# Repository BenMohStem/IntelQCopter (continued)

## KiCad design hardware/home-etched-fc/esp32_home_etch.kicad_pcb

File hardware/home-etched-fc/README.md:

# ESP32-S3 single-sided flight-controller carrier

## Current edition: photographed sensor headers, 23 October 2026

This replaces the earlier four-wire sensor ports. The old PCB, mask and README are preserved in `../../archive/hardware/2026-10-23-before-photo-headers/previous-carrier.zip`. Old extracted ZIP folders are **not** current fabrication files.

- [Open native KiCad PCB](esp32_home_etch.kicad_pcb) and [schematic](esp32_home_etch.kicad_sch).
- [Current complete KiCad ZIP](output/IntelQCopter-ESP32-home-etch-KiCad.zip).
- [Three identical text-free A4 masks, 1:1](output/pdf/etch-mask-3-copies-A4-1to1.pdf).
- [Assembly view](assembly-preview.png), [pin map](connector-map.md), [jumper list](wire-links.csv), [drill coordinates](drill-table.csv).
- [Current original audit results](../../artifacts/hardware/photo-headers-20261023/README.md).

**PCB: 100 x 100 mm; route and etch B.Cu only.** KiCad stores a two-copper-layer board because its file format uses paired copper layers; there are no front-copper routes, vias or plated-layer connections required. All crossings use insulated top wires. Ground is a large solid B.Cu fill, with solid pad joins and circular drill openings, no thermal crosses. Copper under the DevKit antenna region is removed.

## Headers and the photographs

Component-side view. Pin1 of each sensor row is its leftmost pad at x=8 mm; pin numbers increase to the right. These are **2.54 mm solder/header landings** in the photographed signal order, not verified body/mounting-hole models. Mount the sensor boards separately and solder wires signal-to-signal. Do not flip a module onto the carrier just because its pin count matches: the photo may show its opposite face, and its body may overlap neighbouring parts.

| Carrier | Module | Pins1 through last, left to right |
|---|---|---|
| J4, y=45 mm | GY-521 MPU6050, 8 pins | VCC=3.3V; GND; SCL=GPIO8; SDA=GPIO9; XDA unused; XCL unused; AD0=GND; INT unused |
| J5, y=55 mm | GY-BM280, 6 pins | VCC=3.3V; GND; SCL=GPIO8; SDA=GPIO9; CSB=3.3V **through W24**; SDO=GND |
| J6, y=75 mm | GY-271/HW-246, 5 pins | VCC=3.3V; GND; SCL=GPIO8; SDA=GPIO9; DRDY unused |

The MPU screenshot reads INT,AD0,XCL,XDA,SDA,SCL,GND,VCC from its shown left to right. Start wiring from the printed **VCC** end; do not count from the photograph's left edge. The barometer photo reads VCC,GND,SCL,SDA,CSB,SDO from top to bottom. The magnetometer in the hand photo reads VCC,GND,SCL,SDA,DRDY top to bottom. Unused pins get isolated solder pads; they are not joined to the ground plane.

BMP280 CSB must be high for I2C; W24 provides that connection. SDO low selects0x76. MPU AD0 low selects0x68. The GY-271 label does not establish which magnetometer silicon a seller fitted; confirm HMC5883L versus QMC5883L by chip ID/address before selecting its driver. No firmware driver completion is claimed here.

### LiDAR J13: four large wire-solder holes

The official TOFSense F2 Mini uses four wires. This carrier keeps generous5.08mm spacing,3.2mm round pads and1.2mm drills, so no tiny GH connector is needed on the PCB.

| J13 pin | Carrier signal | Connect LiDAR wire labelled |
|---|---|---|
| 1 | Common GND | GND |
| 2 | Regulated5V via W23 | VCC |
| 3 | FC RX / GPIO6 | LiDAR TX |
| 4 | FC TX / GPIO7 | LiDAR RX |

This is a wire landing order, **not** the pin order of the tiny LiDAR plug. Follow the signal labels and official plug diagram. The real F2 Mini reference is four pins; a different five-wire device needs its model/label checked before its fifth wire is assigned. Do not guess a fifth power or mode signal.

## ESP32-S3 assignments

The carrier fits the genuine/reference **Espressif ESP32-S3-DevKitC-1, 2x22 pins**,22.86mm row spacing,2.54mm pitch. A different ESP32-S3 clone is not guaranteed to fit. The chip datasheet specifies GPIO functions; the **DevKit** documentation determines header positions. All four published DevKit GND header pins connect directly to the common copper.

| Function | GPIO | Notes |
|---|---|---|
| Shared I2C SDA / SCL | 9 / 8 | 3.3V pull-ups only |
| ESC FL / FR / RR / RL signal | 12 / 1 / 2 / 14 | Through220ohm; ESC grounds common, no ESC power carried |
| Companion UART TX / RX | 17 / 18 | J12 pins1/2; companion RX/TX respectively; pin3GND |
| LiDAR UART RX / TX | 6 / 7 | J13 pins3/4; UART levels3.3V |
| Battery voltage ADC / current ADC | 4 / 5 | Low-current measurement only |

Assignments keep the existing project firmware GPIO mapping; **no firmware changes are included in this PCB revision**. Avoid using a raw ESP32 chip pin number as a DevKit header number. Boot straps, USB and flash/PSRAM pins are not used for these signals. The current project LiDAR/magnetometer hardware interfaces remain unvalidated. Motor arming remains disabled.

## Supply and assembly

1. Fit **all14 insulated wire links** exactly as `wire-links.csv`, including W24 for BMP280 CSB. A colour line in the assembly image is a real insulated wire, never a copper track on the component side.
2. J3 accepts an **external regulated5V** source. Never connect a3S pack directly there. Motor/ESC current goes through the separate rated PDB. This carrier is not a high-current battery switch or BMS.
3. W21 connects external5V to the DevKit5V input. **Remove W21 before powering the DevKit by USB**. W23 supplies LiDAR5V from the external regulator, not from the3.3V sensor rail.
4. Sensor VCC and I2C logic are3.3V. Check voltage at each actual module's chip supply after its onboard regulator; unknown breakout LDOs may drop too much voltage from3.3V input. No5V I2C pull-up is acceptable at ESP32 GPIOs. Check combined parallel module pull-ups; remove redundant ones if the measured equivalent resistance exceeds the bus sink-current capability. At3.3V,1kohm draws about2.9mA at a0.4V low level.
5. J7 is pack-voltage **sense only**.47kohm/10kohm gives approximately2.21V at12.6V pack voltage, followed by1kohm/100nF filtering. Disconnect sense when the MCU is unpowered; no powered-off clamp isolation is provided. J14 expects a conditioned0-2.5V current signal; its external transducer has not been selected.
6. Use the fit/drill sheet and actual parts before etching.2.54mm rows require smaller1.94mm pads/1.1mm holes to preserve0.60mm copper gaps. Other wire pads are3.2mm/1.2mm. Tracks are at least0.8mm; signal tracks normally1mm. Hand drilling still needs centring.

## Print and etch

Print the **current** PDF with **Actual size /100%**, no fit-to-page. It contains3 copies, no text. Black is retained copper, white is removed copper, and drill centres stay white. The artwork is component-view orientation; pressing the toner side face-down onto bottom copper supplies the required reversal. Do not apply a second mirror. Measure22.86mm between the two DevKit header rows, or the separate20mm calibration ruler before transfer; there is no board-edge line in the text-free mask. Digital1:1 scale is checked; your printer's physical output is not measured here.

Refresh the native B.Cu zone in KiCad with `B` after editing. For a native plot use B.Cu only, black positive, board scale1.0, disable footprint values/references and plot drill marks. The delivered PDF is generated directly from filled native copper and subtracts complete white drill circles; it does not include silkscreen or thermal relief crosses.

## Evidence and remaining limits

Native KiCad DRC/ERC, schematic/netlist comparison and rendered-mask checks report actual results in the dated evidence directory. They check the digital board and explicit wire links. They do not validate unknown module internals, physical fit, regulator performance, a manufactured board, RF behaviour or flight safety. No flight/hardware test was performed for this PCB correction.

References: [Espressif DevKit header map](https://docs.espressif.com/projects/esp-dev-kits/en/latest/esp32s3/esp32-s3-devkitc-1/user_guide_v1.0.html), [ESP32-S3 datasheet](https://www.espressif.com/sites/default/files/documentation/esp32-s3_datasheet_en.pdf), [Bosch BMP280 I2C circuit](https://www.bosch-sensortec.com/media/boschsensortec/downloads/datasheets/bst-bmp280-ds001.pdf), [Nooploop wire sequence](https://support.nooploop.com/tofsense/hardware/). Sensor breakout signal order additionally follows the user photos; personal screenshots are not published.

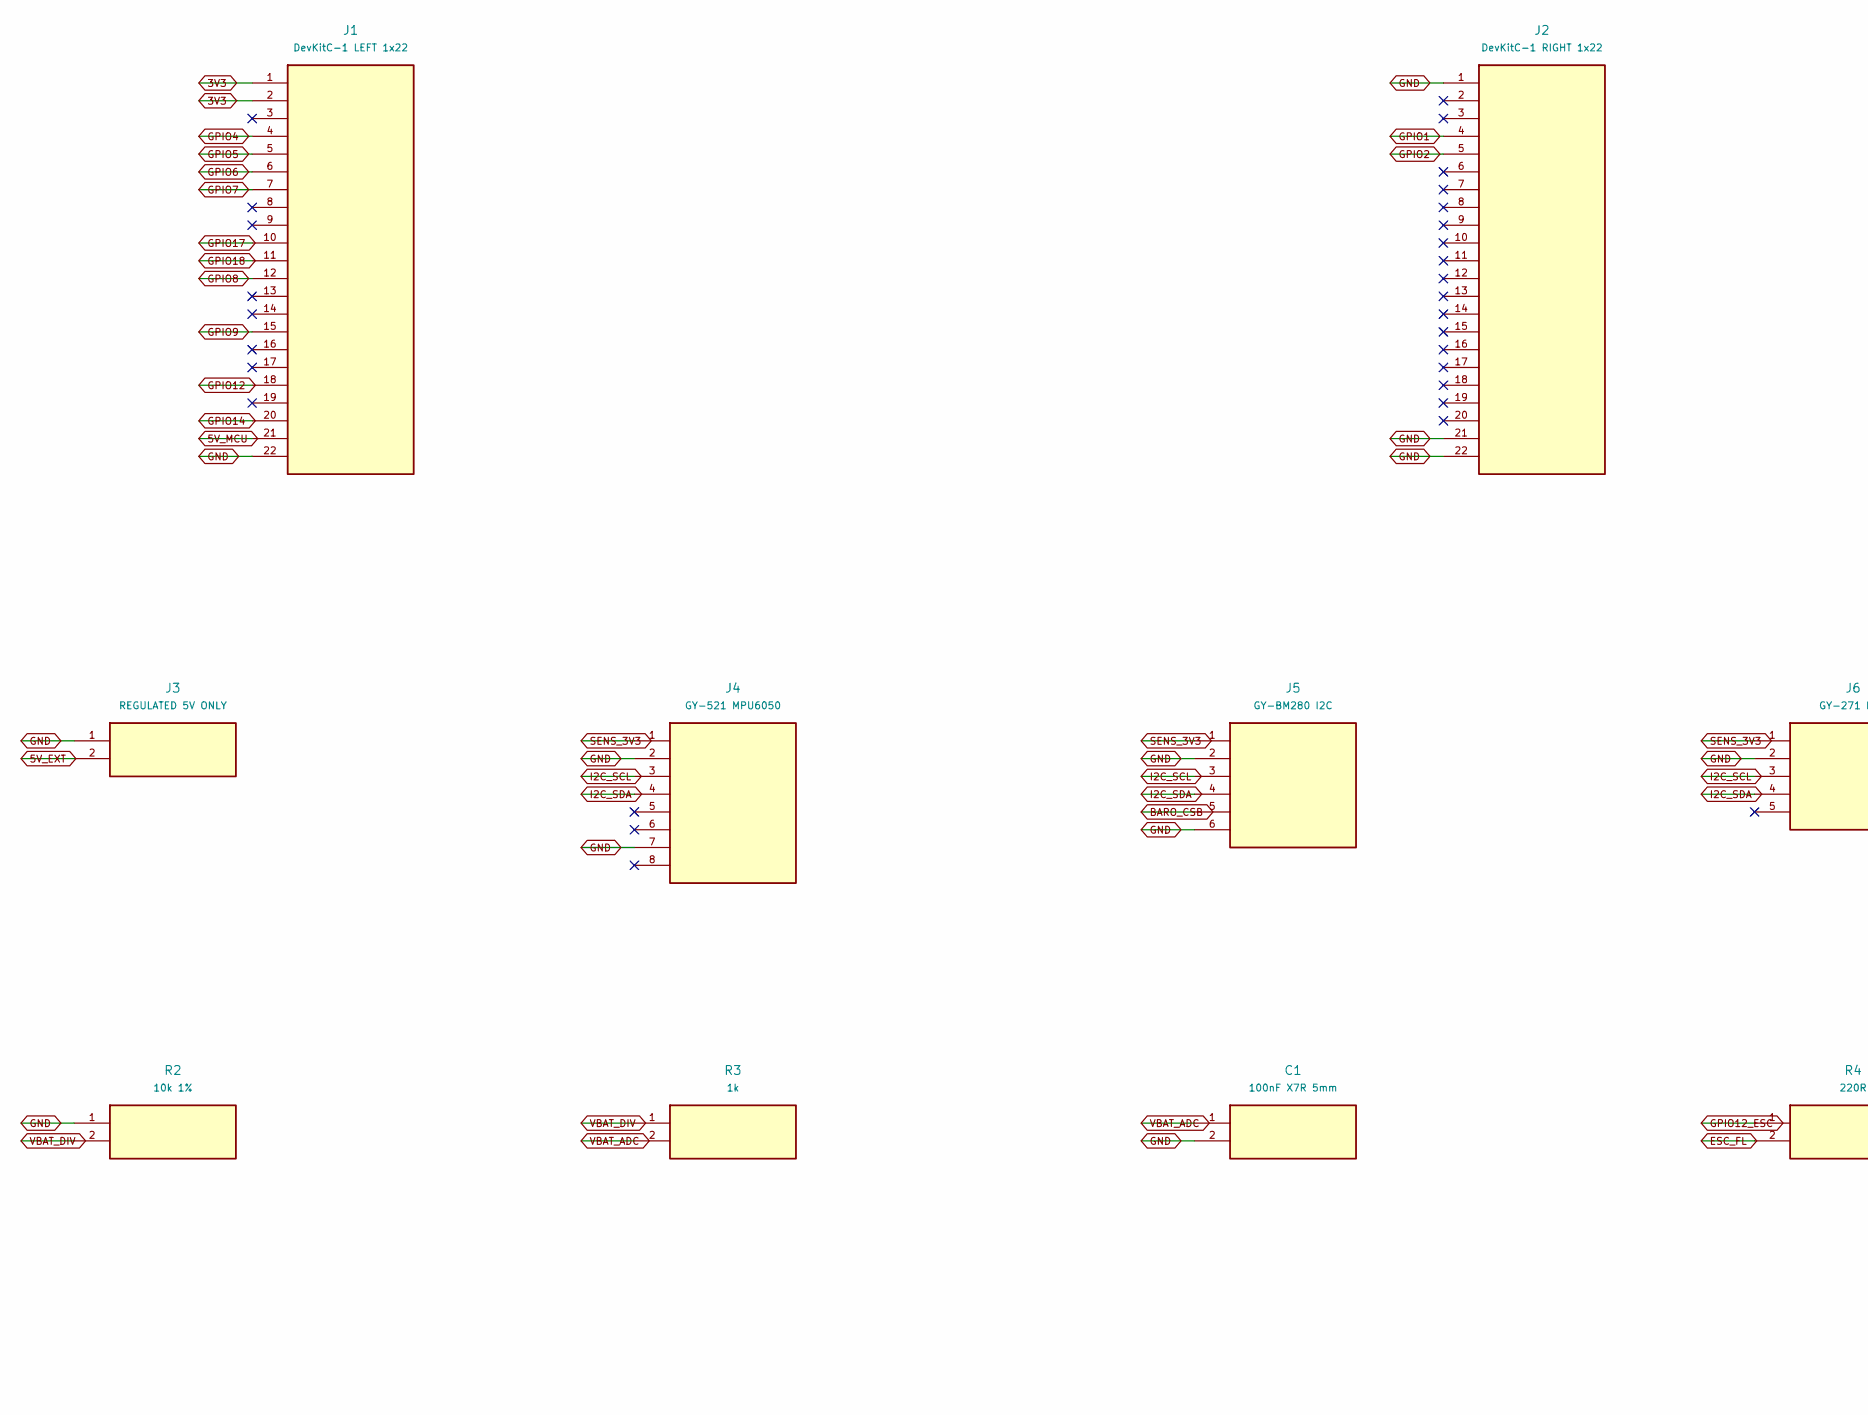
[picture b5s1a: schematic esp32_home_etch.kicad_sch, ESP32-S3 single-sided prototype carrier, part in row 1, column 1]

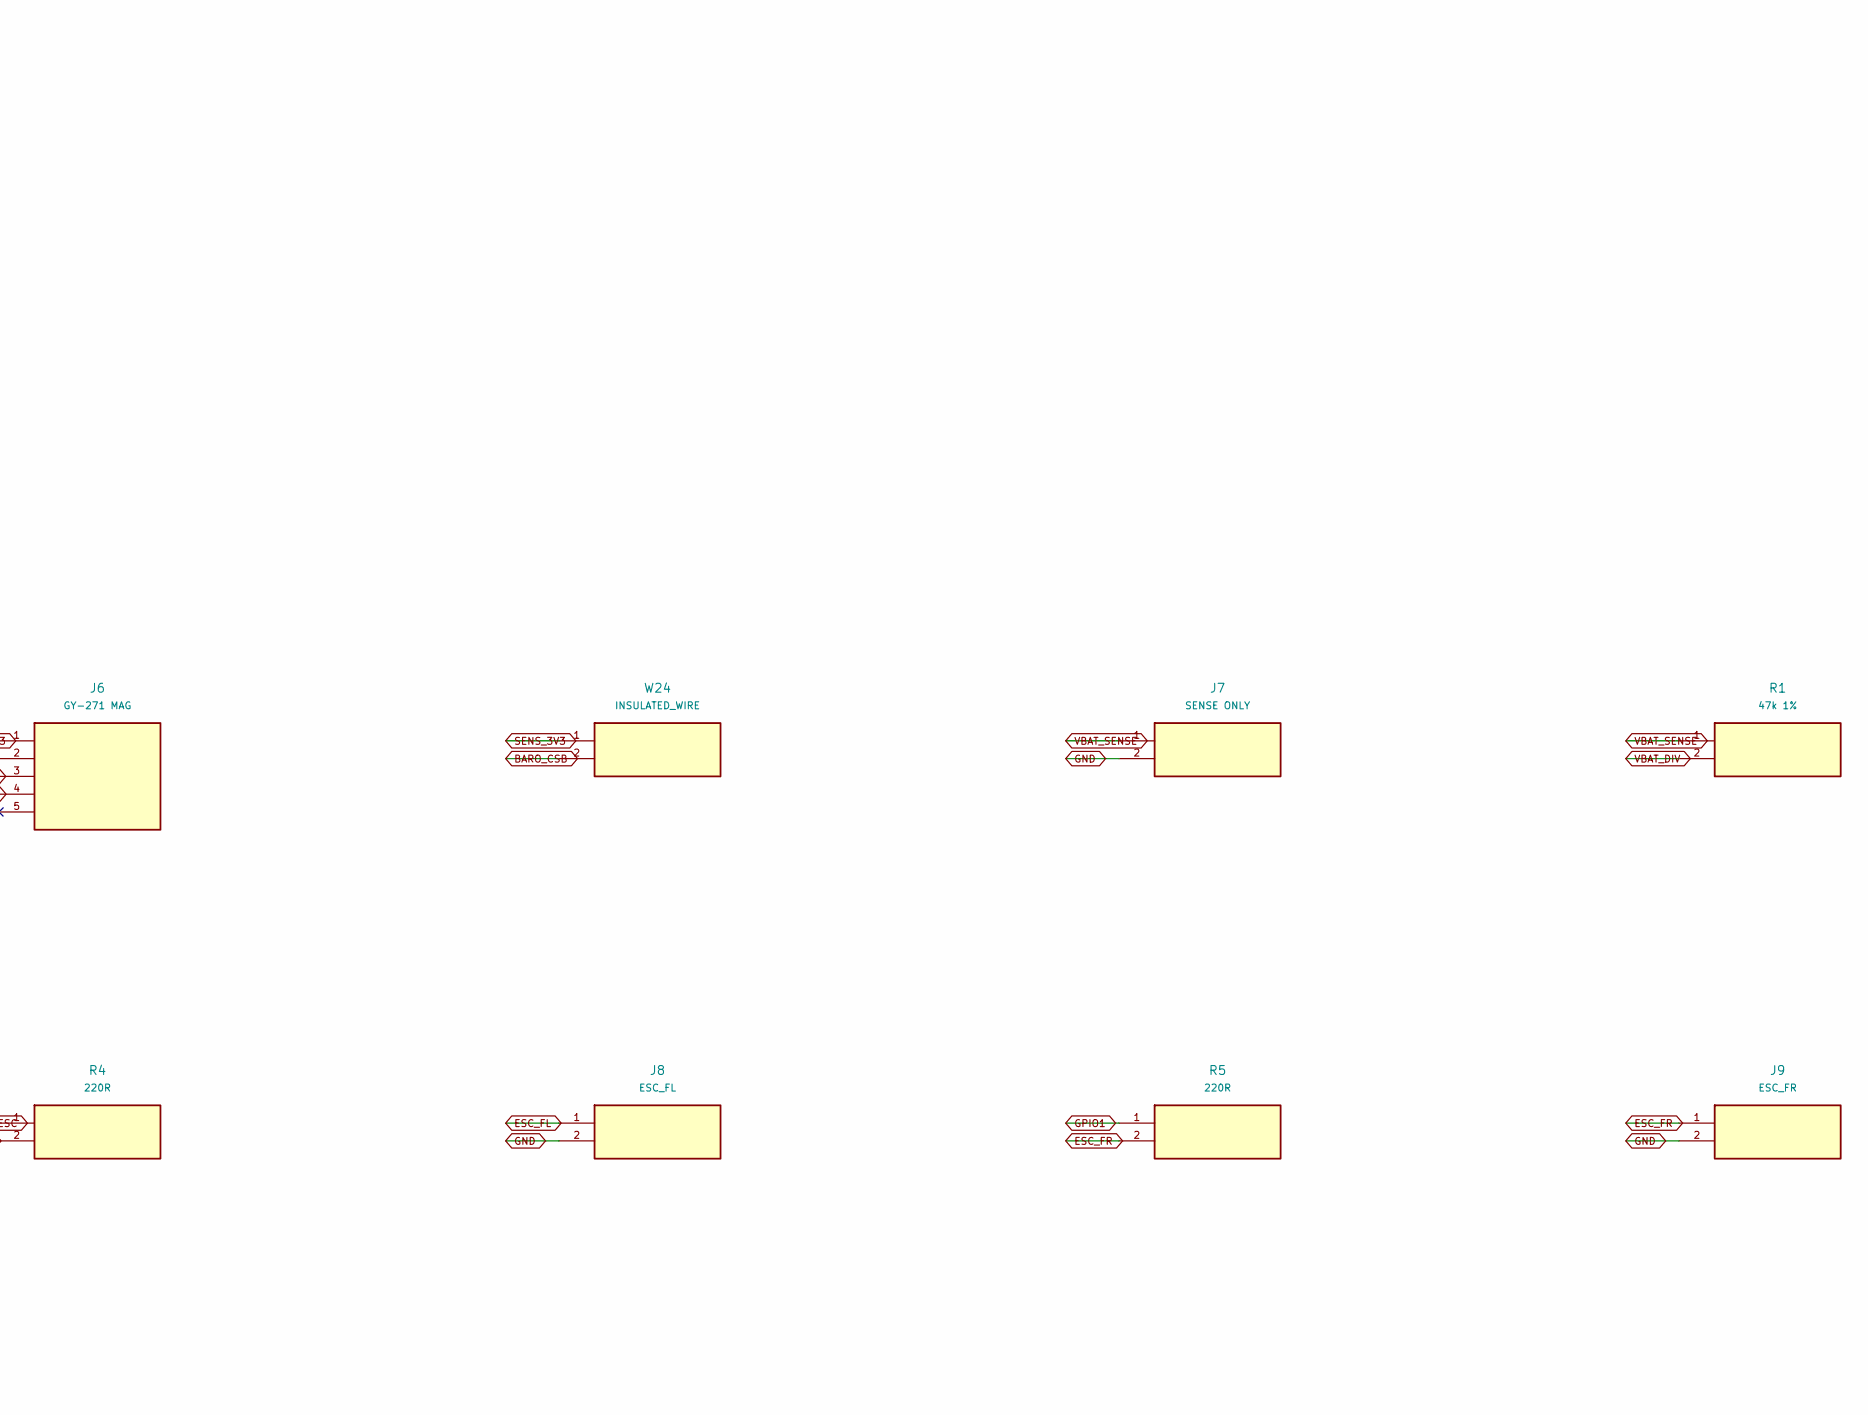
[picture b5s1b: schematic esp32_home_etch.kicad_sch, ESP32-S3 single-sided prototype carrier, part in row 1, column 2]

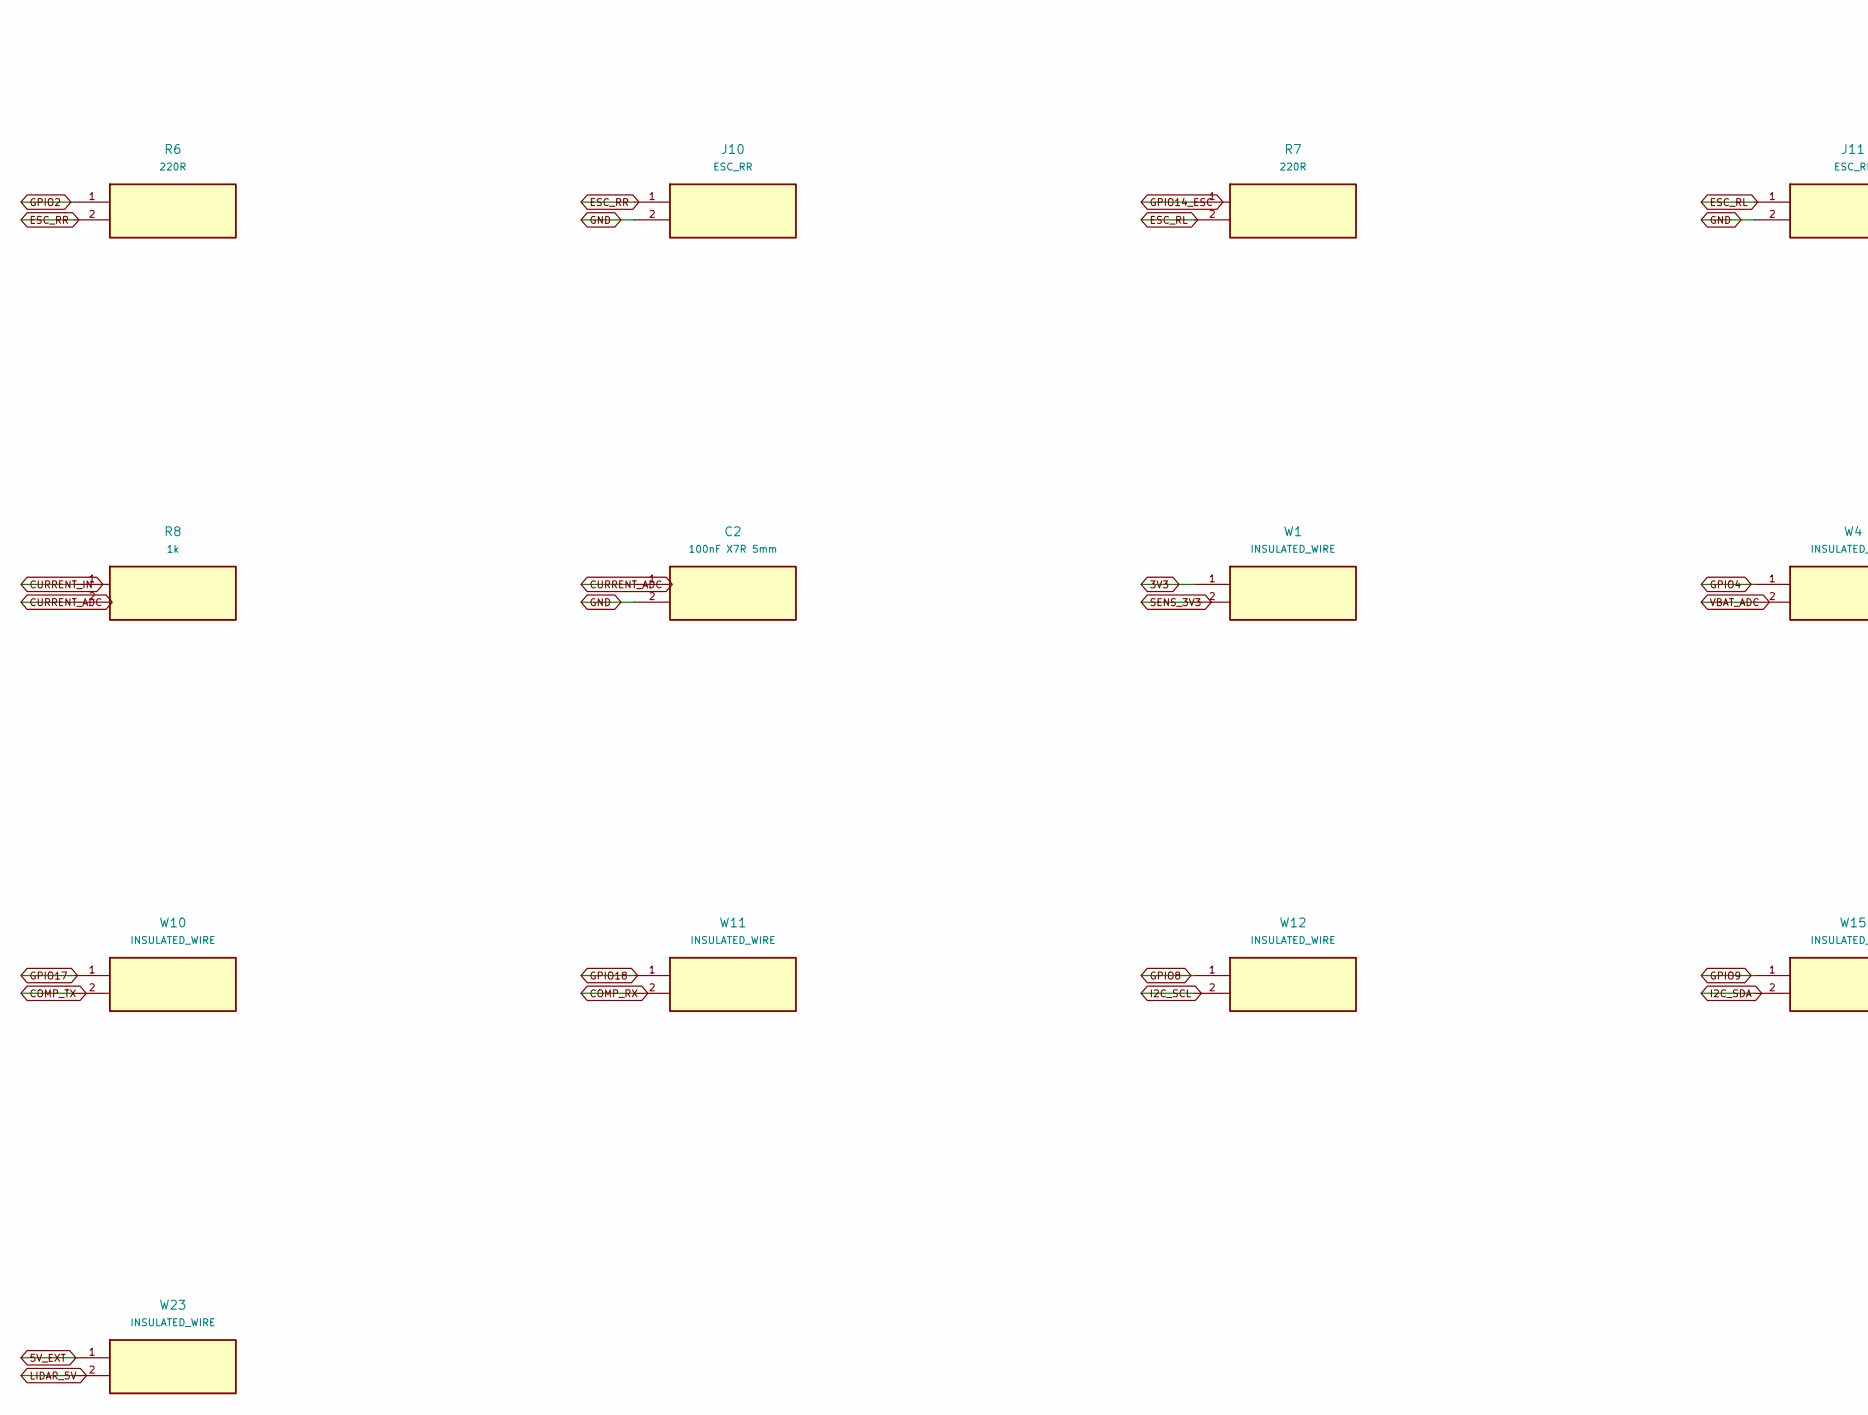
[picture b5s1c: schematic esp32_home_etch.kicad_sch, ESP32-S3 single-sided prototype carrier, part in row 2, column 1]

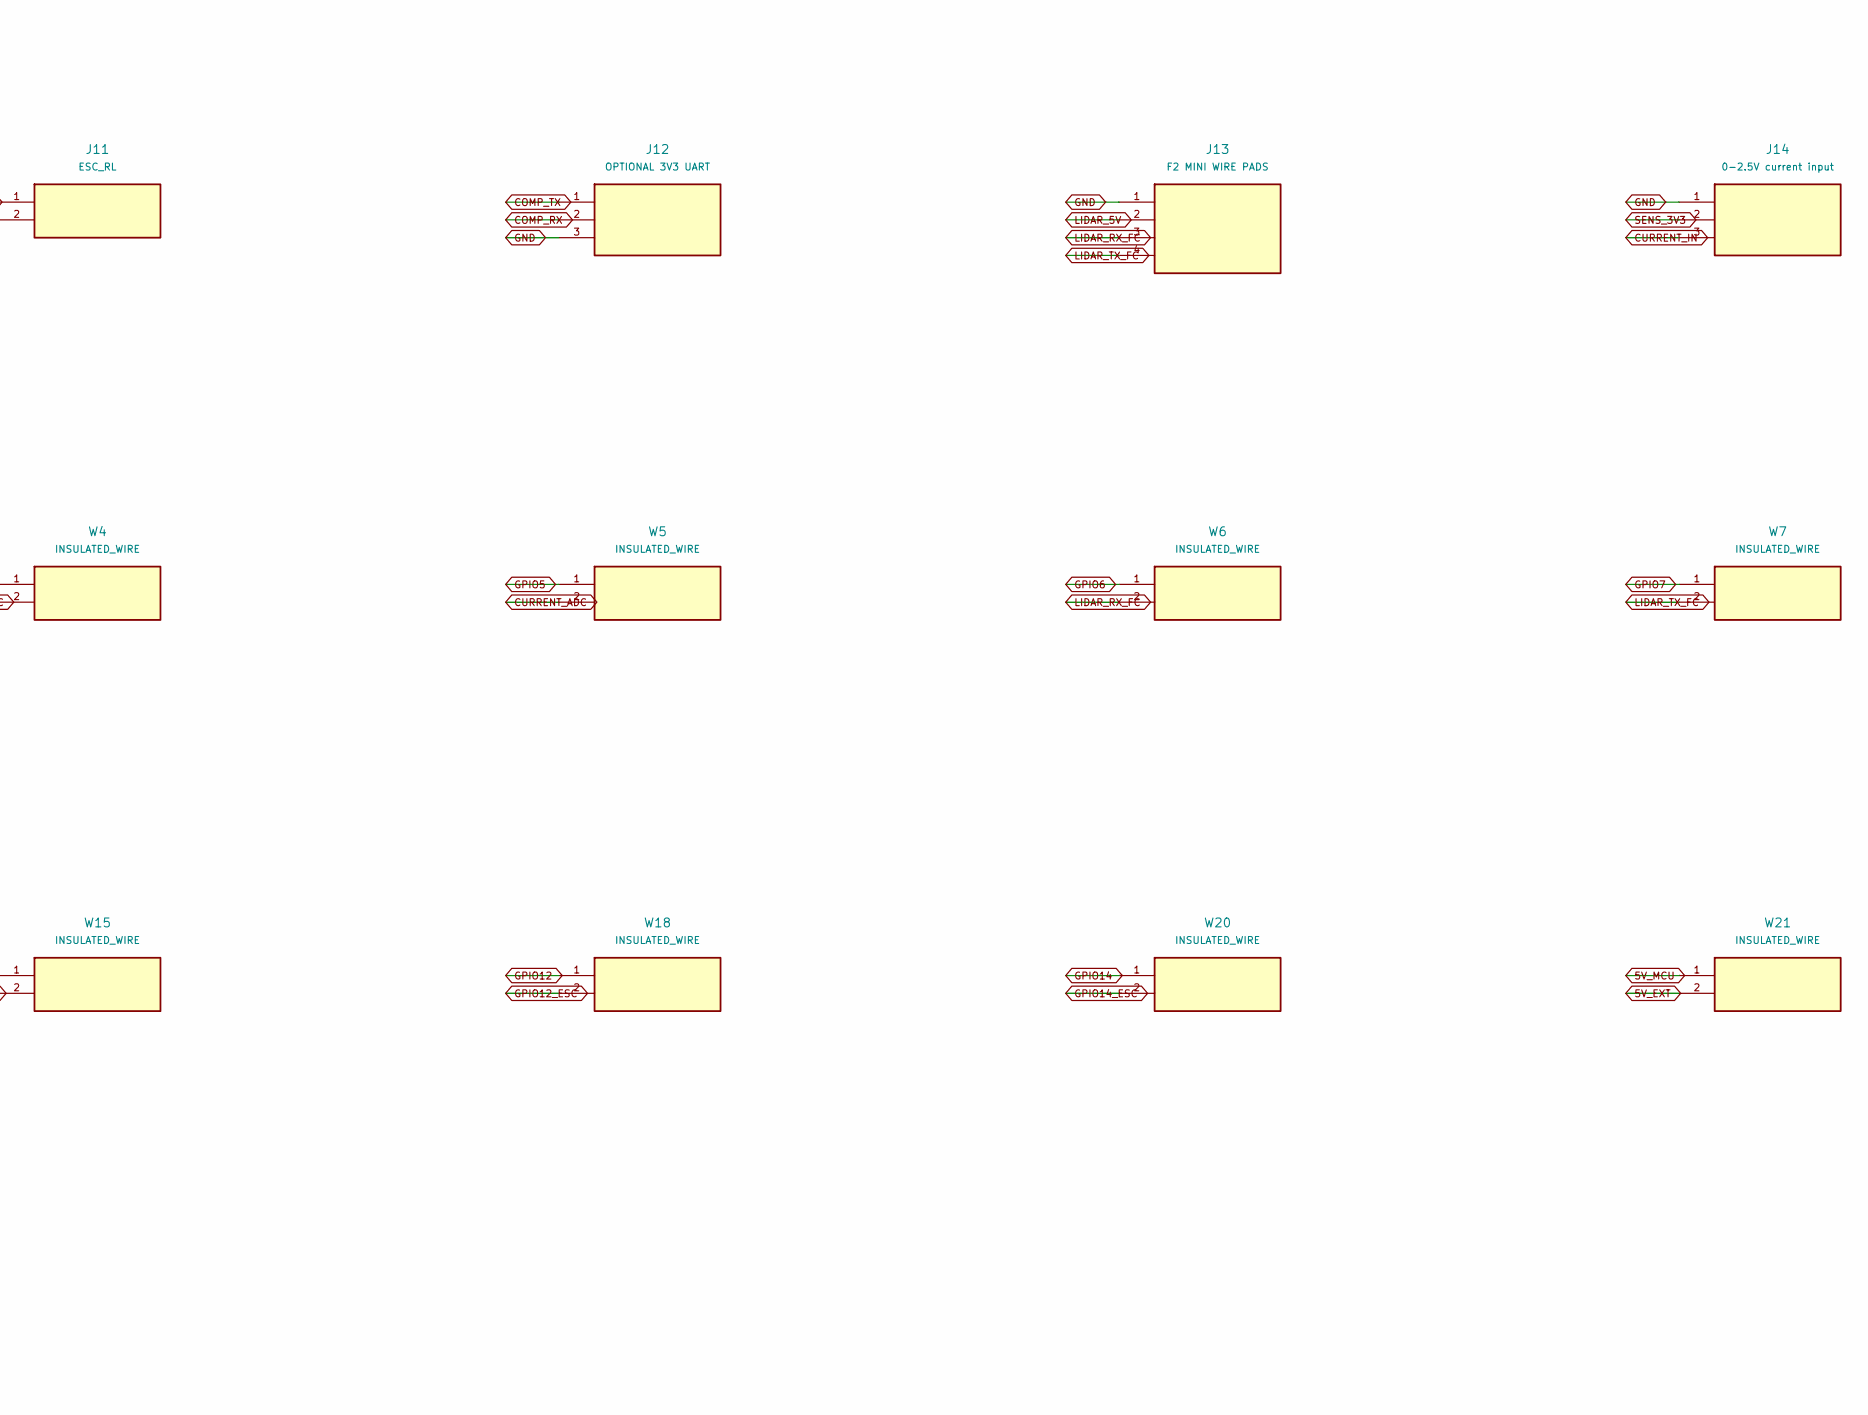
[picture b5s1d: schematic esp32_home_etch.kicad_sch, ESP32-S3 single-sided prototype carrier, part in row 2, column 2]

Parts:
C1: 100nF X7R 5mm; C1
C2: 100nF X7R 5mm; C2
J1: DevKitC-1 LEFT 1x22; J1
J2: DevKitC-1 RIGHT 1x22; J2
J3: REGULATED 5V ONLY; J3
J4: GY-521 MPU6050; J4
J5: GY-BM280 I2C; J5
J6: GY-271 MAG; J6
J7: SENSE ONLY; J7
J8: ESC_FL; J8
J9: ESC_FR; J9
J10: ESC_RR; J10
J11: ESC_RL; J11
J12: OPTIONAL 3V3 UART; J12
J13: F2 MINI WIRE PADS; J13
J14: 0-2.5V current input; J14
R1: 47k 1%; R1
R2: 10k 1%; R2
R3: 1k; R3
R4: 220R; R4
R5: 220R; R5
R6: 220R; R6
R7: 220R; R7
R8: 1k; R8
W1: INSULATED_WIRE; W1
W4: INSULATED_WIRE; W4
W5: INSULATED_WIRE; W5
W6: INSULATED_WIRE; W6
W7: INSULATED_WIRE; W7
W10: INSULATED_WIRE; W10
W11: INSULATED_WIRE; W11
W12: INSULATED_WIRE; W12
W15: INSULATED_WIRE; W15
W18: INSULATED_WIRE; W18
W20: INSULATED_WIRE; W20
W21: INSULATED_WIRE; W21
W23: INSULATED_WIRE; W23
W24: INSULATED_WIRE; W24

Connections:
3V3: J1.1, J1.2, W1.1
5V_EXT: J3.2, W21.2, W23.1
5V_MCU: J1.21, W21.1
BARO_CSB: J5.5, W24.2
COMP_RX: J12.2, W11.2
COMP_TX: J12.1, W10.2
CURRENT_ADC: C2.1, R8.2, W5.2
CURRENT_IN: J14.3, R8.1
ESC_FL: J8.1, R4.2
ESC_FR: J9.1, R5.2
ESC_RL: J11.1, R7.2
ESC_RR: J10.1, R6.2
GND: C1.2, C2.2, J1.22, J2.1, J2.21, J2.22, J3.1, J4.2, J4.7, J5.2, J5.6, J6.2, J7.2, J8.2, J9.2, J10.2, J11.2, J12.3, J13.1, J14.1, R2.1
GPIO1: J2.4, R5.1
GPIO2: J2.5, R6.1
GPIO4: J1.4, W4.1
GPIO5: J1.5, W5.1
GPIO6: J1.6, W6.1
GPIO7: J1.7, W7.1
GPIO8: J1.12, W12.1
GPIO9: J1.15, W15.1
GPIO12: J1.18, W18.1
GPIO12_ESC: R4.1, W18.2
GPIO14: J1.20, W20.1
GPIO14_ESC: R7.1, W20.2
GPIO17: J1.10, W10.1
GPIO18: J1.11, W11.1
I2C_SCL: J4.3, J5.3, J6.3, W12.2
I2C_SDA: J4.4, J5.4, J6.4, W15.2
LIDAR_5V: J13.2, W23.2
LIDAR_RX_FC: J13.3, W6.2
LIDAR_TX_FC: J13.4, W7.2
SENS_3V3: J4.1, J5.1, J6.1, J14.2, W1.2, W24.1
VBAT_ADC: C1.1, R3.2, W4.2
VBAT_DIV: R1.2, R2.2, R3.1
VBAT_SENSE: J7.1, R1.1

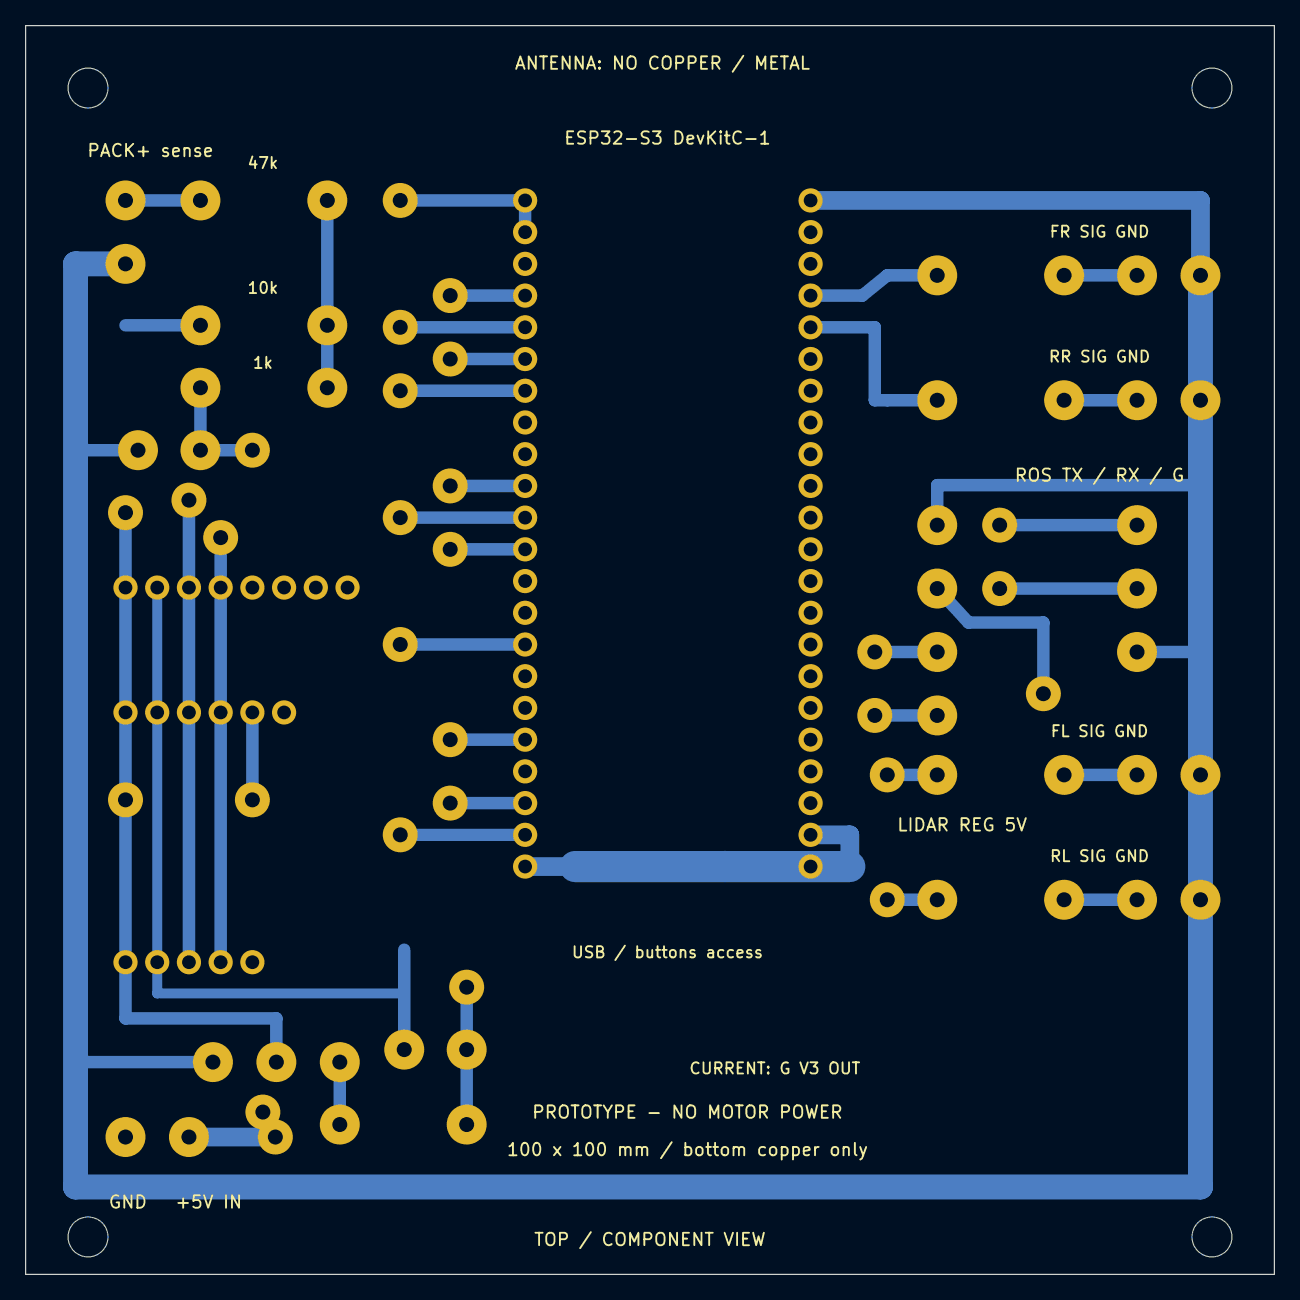
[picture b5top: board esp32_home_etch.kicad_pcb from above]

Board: 2 copper layers, 100.0 x 100.0 mm, 42 parts (0 on the bottom side), 36 nets.

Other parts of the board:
H1, H2, H3, H4: (no value)

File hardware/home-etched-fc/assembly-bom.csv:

Reference,Role,Value,Pad_mm,Drill_mm
J1,U1L,DevKitC-1 LEFT 1x22,1.94,1.1
J2,U1R,DevKitC-1 RIGHT 1x22,1.94,1.1
J3,J_PWR,REGULATED 5V ONLY,3.2,1.2
J4,J_IMU,GY-521 MPU6050,1.94,1.1
J5,J_BARO,GY-BM280 I2C,1.94,1.1
J6,J_MAG,GY-271 MAG,1.94,1.1
W24,W24,INSULATED_WIRE,2.8,1.2
J7,J_BAT,SENSE ONLY,3.2,1.2
R1,R_VTOP,47k 1%,3.2,1.2
R2,R_VBOTTOM,10k 1%,3.2,1.2
R3,R_VFILTER,1k,3.2,1.2
C1,C_VFILTER,100nF X7R 5mm,3.2,1.2
R4,R_FL,220R,3.2,1.2
J8,J_FL,ESC_FL,3.2,1.2
R5,R_FR,220R,3.2,1.2
J9,J_FR,ESC_FR,3.2,1.2
R6,R_RR,220R,3.2,1.2
J10,J_RR,ESC_RR,3.2,1.2
R7,R_RL,220R,3.2,1.2
J11,J_RL,ESC_RL,3.2,1.2
J12,J_ROS,OPTIONAL 3V3 UART,3.2,1.2
J13,J_LIDAR,F2 MINI WIRE PADS,3.2,1.2
J14,J_CURRENT,0-2.5V current input,3.2,1.2
R8,R_IFILTER,1k,3.2,1.2
C2,C_IFILTER,100nF X7R 5mm,3.2,1.2
W1,W1,INSULATED_WIRE,2.8,1.2
W4,W4,INSULATED_WIRE,2.8,1.2
W5,W5,INSULATED_WIRE,2.8,1.2
W6,W6,INSULATED_WIRE,2.8,1.2
W7,W7,INSULATED_WIRE,2.8,1.2
W10,W10,INSULATED_WIRE,2.8,1.2
W11,W11,INSULATED_WIRE,2.8,1.2
W12,W12,INSULATED_WIRE,2.8,1.2
W15,W15,INSULATED_WIRE,2.8,1.2
W18,W18,INSULATED_WIRE,2.8,1.2
W20,W20,INSULATED_WIRE,2.8,1.2
W21,W21,INSULATED_WIRE,2.8,1.2
W23,W23,INSULATED_WIRE,2.8,1.2

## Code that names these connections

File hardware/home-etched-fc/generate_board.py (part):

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
for a,b in [((0,0),(100,0)),((100,0),(100,100)),((100,100),(0,100)),((0,100),(0,0))]:line(a,b)
# Socket numbering is the actual two header rows, viewed FROM COMPONENT SIDE.
L=['3V3','3V3','','GPIO4','GPIO5','GPIO6','GPIO7','','','GPIO17','GPIO18','GPIO8','','','GPIO9','','','GPIO12','','GPIO14','5V_MCU','GND']
R=['GND','','','GPIO1','GPIO2','','','','','','','','','','','','','','','','','']
R[20]=R[21]='GND'
fp('U1L','DevKitC-1 LEFT 1x22',[(i+1,40,14+i*2.54,n) for i,n in enumerate(L)],1.94,1.1)
fp('U1R','DevKitC-1 RIGHT 1x22',[(i+1,62.86,14+i*2.54,n) for i,n in enumerate(R)],1.94,1.1)
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route('VBAT_ADC',[(14,29),(14,34),(18.16,34)])
text('47k',19,11,.9);text('10k',19,21,.9);text('1k',19,27,.9)
# ESC signal resistors and signal-ground returns; BEC positive omitted.
for ref,y,sig,gpio in [('FL',60,'ESC_FL','GPIO12'),('FR',20,'ESC_FR','GPIO1'),('RR',30,'ESC_RR','GPIO2'),('RL',70,'ESC_RL','GPIO14')]:
 fp('R_'+ref,'220R',[(1,73,y,gpio if ref in ('FR','RR') else gpio+'_ESC'),(2,83.16,y,sig)])
 fp('J_'+ref,sig,[(1,89,y,sig),(2,94.08,y,'GND')]);route(sig,[(83.16,y),(89,y)])
 text(ref+' SIG GND',86,y-3.5,.9)
route('GPIO1',[(62.86,21.62),(67,21.62),(69,20)])
route('GPIO1',[(69,20),(73,20)])
route('GPIO2',[(62.86,24.16),(68,24.16),(68,30),(69,30)])
route('GPIO2',[(69,30),(73,30)])
# Optional ROS2: signal only, no companion power carried by PCB.
fp('J_ROS','OPTIONAL 3V3 UART',[(1,89,40,'COMP_TX'),(2,89,45.08,'COMP_RX'),(3,89,50.16,'GND')])
route('COMP_TX',[(78,40),(89,40)]);route('COMP_RX',[(78,45.08),(89,45.08)]);route('GND',[(89,50.16),(94.08,50.16)])
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 route(gpio,[(40,y),(x,y)],1.)
 wire('W'+str(idx),(x,y),gpio,end,external,desc)
route('5V_EXT',[(13.08,89),(20,89)],1.5)
route('GPIO12_ESC',[(69,60),(73,60)])
route('GPIO14_ESC',[(69,70),(73,70)])
# Four documented DevKit GND pins connect directly to B.Cu GND, without W22.
# Left J1.22 and right J2.1/J2.21/J2.22 use same-net copper plus the large fill.
route('GND',[(40,67.34),(44,67.34)],1.5)
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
